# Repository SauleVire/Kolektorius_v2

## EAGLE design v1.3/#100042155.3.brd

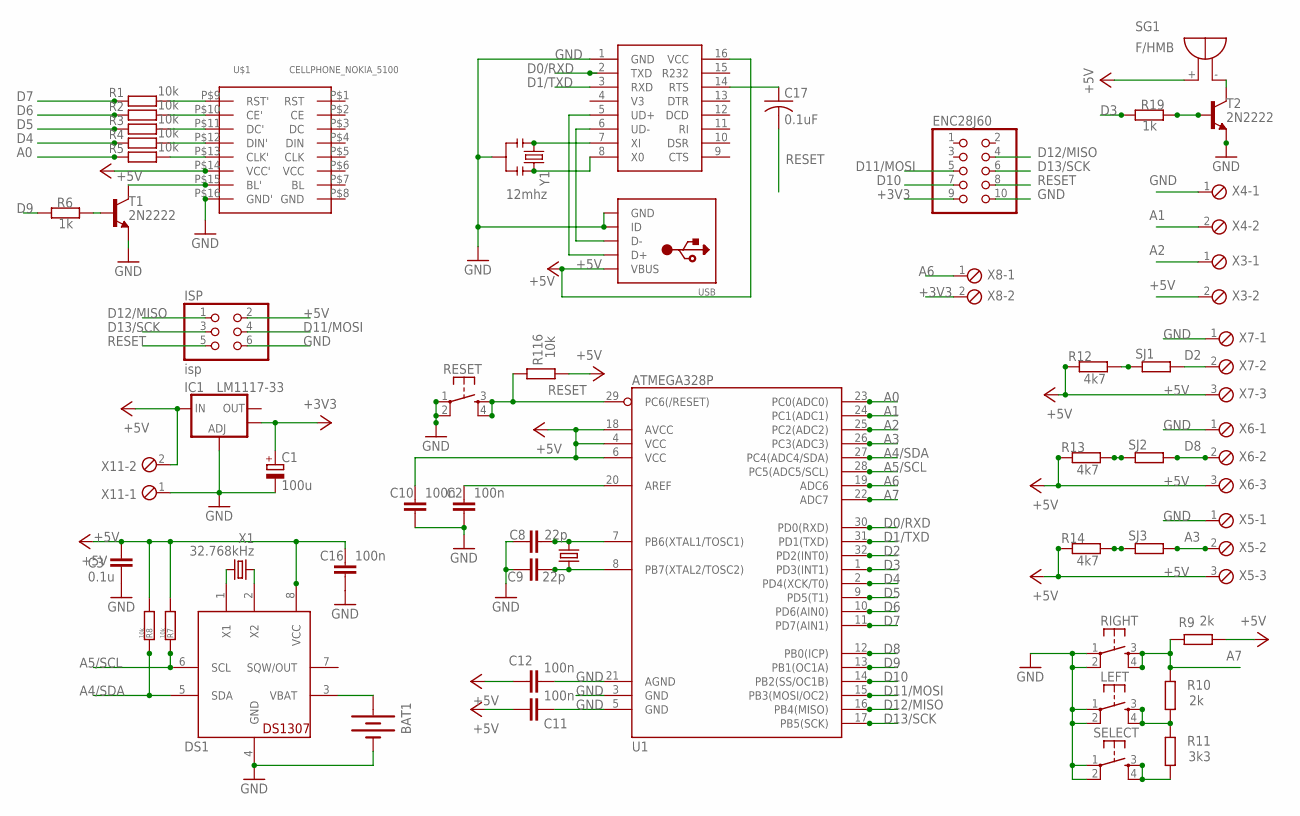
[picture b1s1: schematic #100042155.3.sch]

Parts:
BAT1: BATTCOM_20MM_PTH
C1: 100u; E2-5
C2, C10, C11, C12, C16: 100n; C0805
C3: 0.1u; C0805
C8, C9: 22p; C0805
C17: 0.1uF; C0805K
DS1: DS1307; SO08
ENC28J60: 2X05
IC1: LM1117-33; SOT223
ISP: isp; 2X03
LEFT: TACTILE-PTH
R1, R2, R3, R4, R5, R7, R8, R116: 10k; R0805
R6, R19: 1k; R0805
R9, R10: 2k; R0805
R11: 3k3; R0805
R12, R13, R14: 4k7; R0805
RESET: TAC_SWITCHPTH; TACTILE-PTH
RIGHT: TACTILE-PTH
SELECT: TACTILE-PTH
SG1: F/HMB
SJ1, SJ2, SJ3: R0402
T1, T2: 2N2222; TO92-EBC-OVAL
U1: ATMEGA328P; TQFP32-08
U$1: CELLPHONE_NOKIA_5100; CELLPHONE_NOKIA_5100_SPARKFUN
U$2: CH340G; SO016
USB: USB-MINIB-THM-MOLEX
X1: 32.768kHz; TC26H
X2: 16MHz; HC49US
X3, X4, X8, X11: 2POL254
X5, X6, X7: 3POL254
Y1: 12mhz; RESONATOR-PTH

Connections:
+3V3: C1.+, ENC28J60.9, IC1.4 (OUT), X8.2
+5V: C3.1, C10.1, C11.2, C12.2, C16.1, DS1.8 (VCC), IC1.3 (IN), ISP.2, R7.2, R8.2, R9.2, R12.1, R13.1, R14.1, R116.2, SG1.+, U1.4 (VCC), U1.6 (VCC), U1.18 (AVCC), U$1.P$14 (VCC'), U$2.16 (VCC), USB.VBUS, X3.2, X5.3, X6.3, X7.3, X11.2
A0: R5.1, U1.23 (PC0(ADC0))
A1: U1.24 (PC1(ADC1)), X4.2
A2: U1.25 (PC2(ADC2)), X3.1
A3: SJ3.2, U1.26 (PC3(ADC3)), X5.2
A4/SDA: DS1.5 (SDA), R8.1, U1.27 (PC4(ADC4/SDA))
A5/SCL: DS1.6 (SCL), R7.1, U1.28 (PC5(ADC5/SCL))
A6: U1.19 (ADC6), X8.1
A7: R9.1, R10.2, RIGHT.3, RIGHT.4, U1.22 (ADC7)
AREF: C2.1, U1.20 (AREF)
D0/RXD: U1.30 (PD0(RXD)), U$2.2 (TXD)
D1/TXD: U1.31 (PD1(TXD)), U$2.3 (RXD)
D2: SJ1.2, U1.32 (PD2(INT0)), X7.2
D3: R19.2, U1.1 (PD3(INT1))
D4: R4.1, U1.2 (PD4(XCK/T0))
D5: R3.1, U1.9 (PD5(T1))
D6: R2.1, U1.10 (PD6(AIN0))
D7: R1.1, U1.11 (PD7(AIN1))
D8: SJ2.2, U1.12 (PB0(ICP)), X6.2
D9: R6.2, U1.13 (PB1(OC1A))
D10: ENC28J60.7, U1.14 (PB2(SS/OC1B))
D11/MOSI: ENC28J60.5, ISP.4, U1.15 (PB3(MOSI/OC2))
D12/MISO: ENC28J60.4, ISP.1, U1.16 (PB4(MISO))
D13/SCK: ENC28J60.6, ISP.3, U1.17 (PB5(SCK))
GND: BAT1.2 (-), C1.-, C2.2, C3.2, C8.1, C9.1, C10.2, C11.1, C12.1, C16.2, DS1.4 (GND), ENC28J60.10, IC1.1 (ADJ), ISP.6, LEFT.1, LEFT.2, RESET.1, RESET.2, RIGHT.1, RIGHT.2, SELECT.1, SELECT.2, T1.E, T2.E, U1.3 (GND), U1.5 (GND), U1.21 (AGND), U$1.P$16 (GND'), U$2.1 (GND), USB.GND, USB.ID, X4.1, X5.1, X6.1, X7.1, X11.1, Y1.2
unnamed: LEFT.3, LEFT.4, R10.1, R11.2
unnamed: R5.2, U$1.P$13 (CLK')
unnamed: R4.2, U$1.P$12 (DIN')
unnamed: R3.2, U$1.P$11 (DC')
unnamed: R2.2, U$1.P$10 (CE')
unnamed: R1.2, U$1.P$9 (RST')
unnamed: BAT1.1 (+), DS1.3 (VBAT)
unnamed: DS1.1 (X1), X1.2
unnamed: U$2.7 (XI), Y1.1
unnamed: U$2.6 (UD-), USB.D-
unnamed: U$2.5 (UD+), USB.D+
unnamed: R13.2, SJ2.1
unnamed: R11.1, SELECT.3, SELECT.4
unnamed: T1.C, U$1.P$15 (BL')
unnamed: R19.1, T2.B
unnamed: R14.2, SJ3.1
unnamed: SG1.-, T2.C
unnamed: DS1.2 (X2), X1.1
unnamed: R12.2, SJ1.1
unnamed: C9.2, U1.8 (PB7(XTAL2/TOSC2)), X2.1
unnamed: C8.2, U1.7 (PB6(XTAL1/TOSC1)), X2.2
unnamed: U$2.8 (X0), Y1.3
unnamed: C17.1, U$2.14 (RTS)
unnamed: R6.1, T1.B
RESET: C17.2, ENC28J60.8, ISP.5, R116.1, RESET.3, RESET.4, U1.29 (PC6(/RESET))

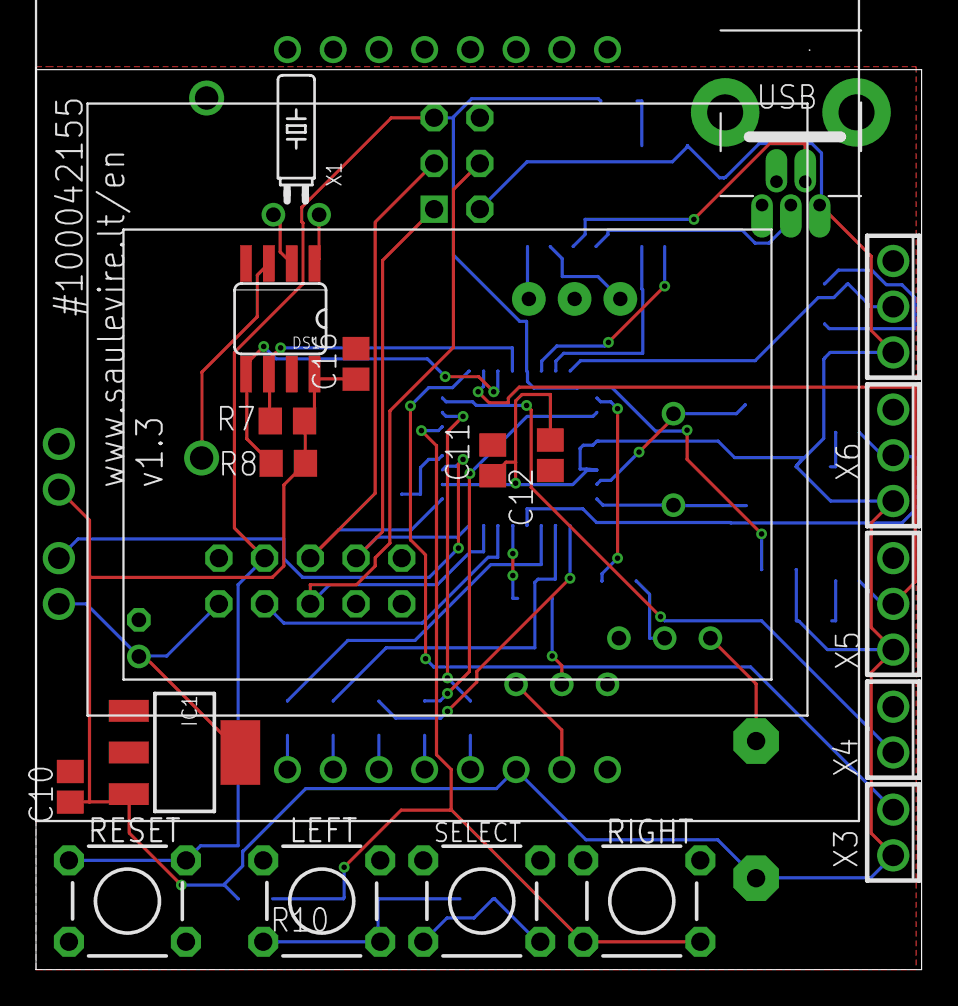
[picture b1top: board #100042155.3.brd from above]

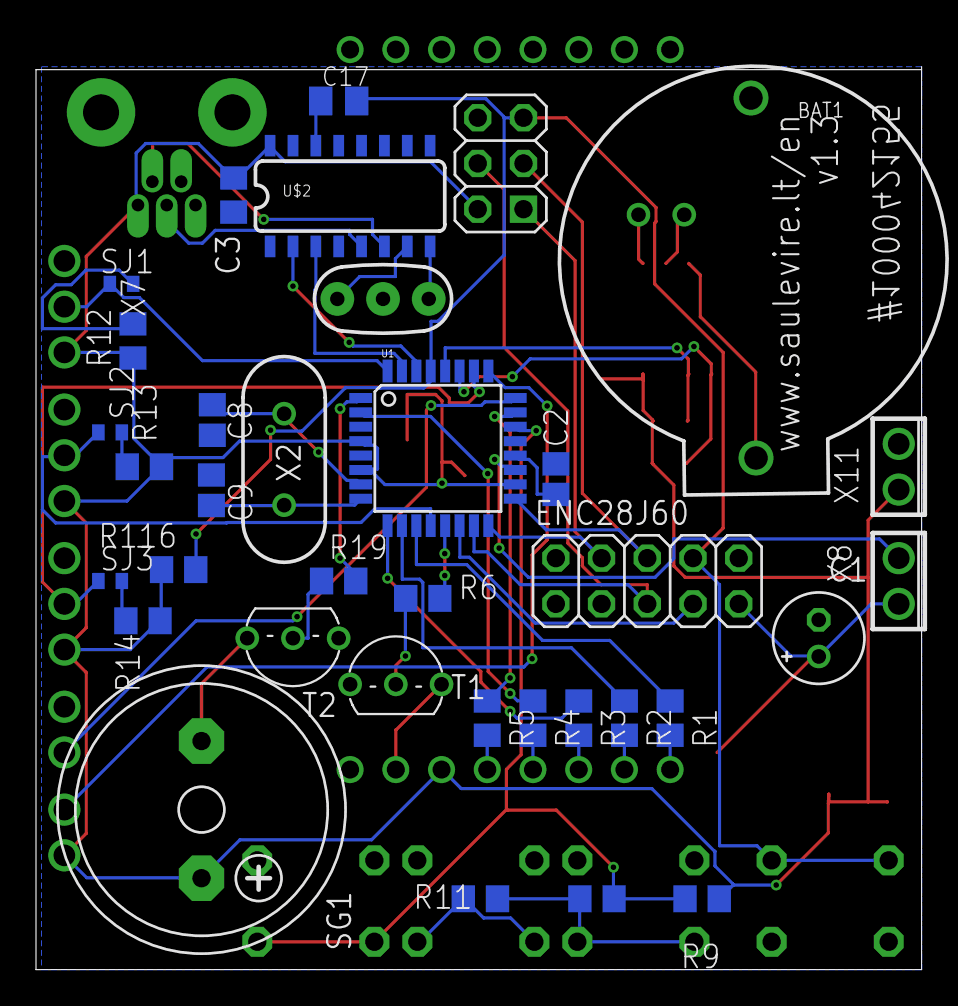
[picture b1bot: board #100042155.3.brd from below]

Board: 2 copper layers, 49.2 x 50.2 mm, 55 parts (35 on the bottom side), 51 nets.

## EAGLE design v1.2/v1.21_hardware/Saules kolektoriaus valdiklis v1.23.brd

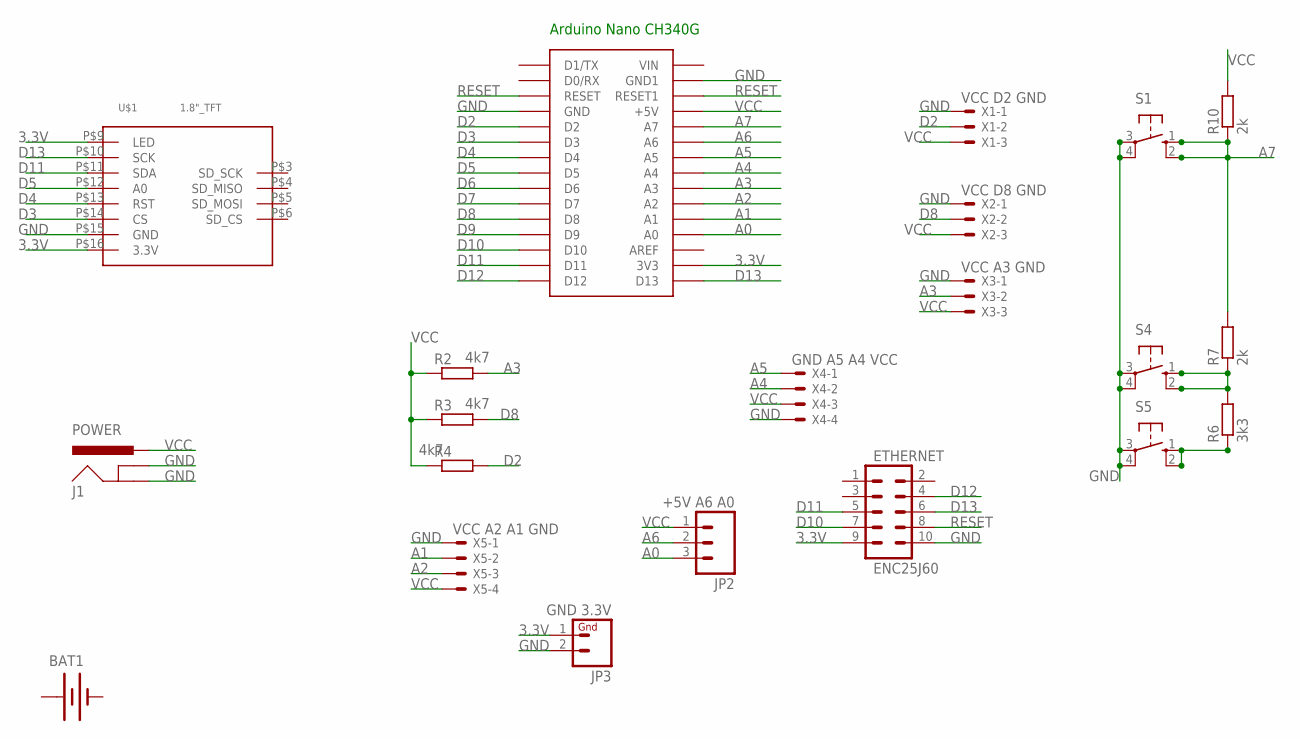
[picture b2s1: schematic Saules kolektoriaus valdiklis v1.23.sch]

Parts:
ARDUINONANOCH340G: ARDUINONANO; PDIP-32
BAT1: BATTERY20PTH; BATTCOM_20MM_PTH
ETHERNET: ENC25J60; AVR_ICSP
J1: POWER; POWER_JACK_PTH_LOCK
JP2: +5V A6 A0; 1X03
JP3: GND 3.3V; 1X02
R2, R3, R4: 4k7; 0207/10
R6: 3k3; 0207/10
R7, R10: 2k; 0207/10
S1, S4, S5: 10-XX; B3F-10XX
U$1: 1.8"_TFT
X1: VCC D2 GND; 22-23-2031
X2: VCC D8 GND; 22-23-2031
X3: VCC A3 GND; 22-23-2031
X4: GND A5 A4 VCC; 22-23-2041
X5: VCC A2 A1 GND; 22-23-2041

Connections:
3.3V: ARDUINONANOCH340G.3V3, ETHERNET.9, JP3.1, U$1.P$9 (LED), U$1.P$16 (3.3V)
+: BAT1.1 (+)
-: BAT1.2 (-)
A0: ARDUINONANOCH340G.A0, JP2.3
A1: ARDUINONANOCH340G.A1, X5.2
A2: ARDUINONANOCH340G.A2, X5.3
A3: ARDUINONANOCH340G.A3, R2.2, X3.2
A4: ARDUINONANOCH340G.A4, X4.2
A5: ARDUINONANOCH340G.A5, X4.1
A6: ARDUINONANOCH340G.A6, JP2.2
A7: ARDUINONANOCH340G.A7, R7.2, R10.1, S1.1 (S), S1.2 (S1)
D2: ARDUINONANOCH340G.D2, R4.2, X1.2
D3: ARDUINONANOCH340G.D3, U$1.P$14 (CS)
D4: ARDUINONANOCH340G.D4, U$1.P$13 (RST)
D5: ARDUINONANOCH340G.D5, U$1.P$12 (A0)
D6: ARDUINONANOCH340G.D6
D7: ARDUINONANOCH340G.D7
D8: ARDUINONANOCH340G.D8, R3.2, X2.2
D9: ARDUINONANOCH340G.D9
D10: ARDUINONANOCH340G.D10, ETHERNET.7
D11: ARDUINONANOCH340G.D11, ETHERNET.5, U$1.P$11 (SDA)
D12: ARDUINONANOCH340G.D12, ETHERNET.4
D13: ARDUINONANOCH340G.D13, ETHERNET.6, U$1.P$10 (SCK)
GND: ARDUINONANOCH340G.GND, ARDUINONANOCH340G.GND1, ETHERNET.10, J1.GND, J1.GNDBREAK, JP3.2, S1.3, S1.4 (P1), S4.3, S4.4 (P1), S5.3, S5.4 (P1), U$1.P$15 (GND), X1.1, X2.1, X3.1, X4.4, X5.1
unnamed: R6.1, S5.1 (S), S5.2 (S1)
unnamed: R6.2, R7.1, S4.1 (S), S4.2 (S1)
RESET: ARDUINONANOCH340G.RESET, ARDUINONANOCH340G.RESET1, ETHERNET.8
VCC: ARDUINONANOCH340G.+5V, J1.PWR, JP2.1, R2.1, R3.1, R4.1, R10.2, X1.3, X2.3, X3.3, X4.3, X5.4

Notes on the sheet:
Arduino Nano CH340G

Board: 2 copper layers, 21 parts (2 on the bottom side), 23 nets, no tracks yet.

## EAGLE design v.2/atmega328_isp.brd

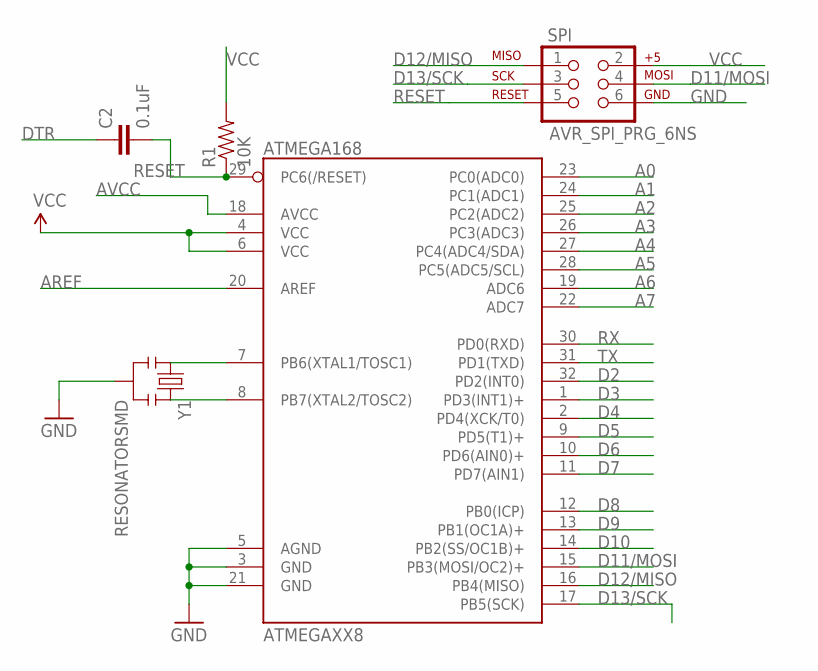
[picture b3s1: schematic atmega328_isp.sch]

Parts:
ATMEGAXX8: ATMEGA168; TQFP32-08
C2: 0.1uF; 0805
R1: 10K; 0805
SPI: AVR_SPI_PRG_6NS; 2X3-NS
Y1: RESONATORSMD; RESONATOR-SMD

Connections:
A0: ATMEGAXX8.23 (PC0(ADC0))
A1: ATMEGAXX8.24 (PC1(ADC1))
A2: ATMEGAXX8.25 (PC2(ADC2))
A3: ATMEGAXX8.26 (PC3(ADC3))
A4: ATMEGAXX8.27 (PC4(ADC4/SDA))
A5: ATMEGAXX8.28 (PC5(ADC5/SCL))
A6: ATMEGAXX8.19 (ADC6)
A7: ATMEGAXX8.22 (ADC7)
AREF: ATMEGAXX8.20 (AREF)
AVCC: ATMEGAXX8.18 (AVCC)
D2: ATMEGAXX8.32 (PD2(INT0))
D3: ATMEGAXX8.1 (PD3(INT1)+)
D4: ATMEGAXX8.2 (PD4(XCK/T0))
D5: ATMEGAXX8.9 (PD5(T1)+)
D6: ATMEGAXX8.10 (PD6(AIN0)+)
D7: ATMEGAXX8.11 (PD7(AIN1))
D8: ATMEGAXX8.12 (PB0(ICP))
D9: ATMEGAXX8.13 (PB1(OC1A)+)
D10: ATMEGAXX8.14 (PB2(SS/OC1B)+)
D11/MOSI: ATMEGAXX8.15 (PB3(MOSI/OC2)+), SPI.4
D12/MISO: ATMEGAXX8.16 (PB4(MISO)), SPI.1
D13/SCK: ATMEGAXX8.17 (PB5(SCK)), SPI.3
DTR: C2.1
GND: ATMEGAXX8.3 (GND), ATMEGAXX8.5 (AGND), ATMEGAXX8.21 (GND), SPI.6, Y1.2
RESET: ATMEGAXX8.29 (PC6(/RESET)), C2.2, R1.1, SPI.5
RX: ATMEGAXX8.30 (PD0(RXD))
TX: ATMEGAXX8.31 (PD1(TXD))
VCC: ATMEGAXX8.4 (VCC), ATMEGAXX8.6 (VCC), R1.2, SPI.2
XTAL1: ATMEGAXX8.7 (PB6(XTAL1/TOSC1)), Y1.1
XTAL2: ATMEGAXX8.8 (PB7(XTAL2/TOSC2)), Y1.3

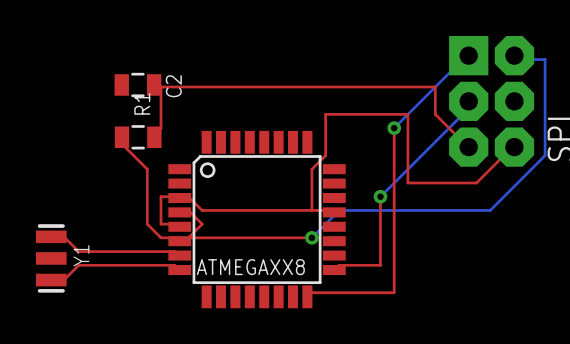
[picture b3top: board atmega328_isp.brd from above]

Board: 2 copper layers, 5 parts (0 on the bottom side), 8 nets.

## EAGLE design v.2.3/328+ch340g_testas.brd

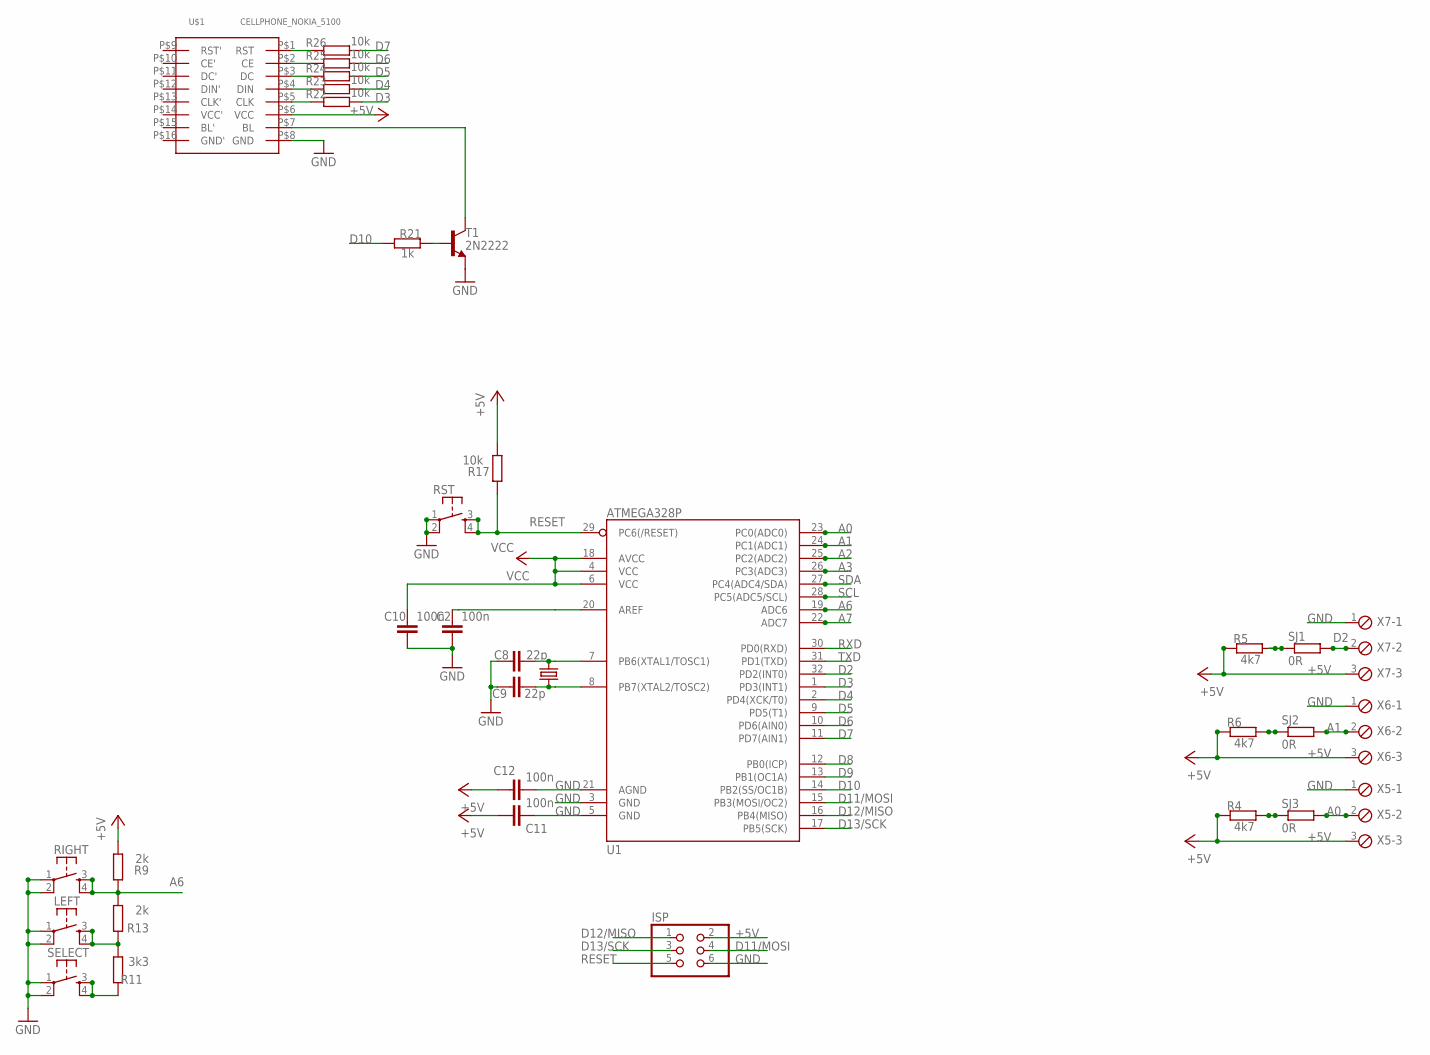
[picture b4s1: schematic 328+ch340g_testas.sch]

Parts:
C2, C10, C11, C12: 100n; C0805
C8, C9: 22p; C0805
ISP: PINHD-2X3; 2X03
LEFT: TAC_SWITCHPTH; TACTILE-PTH
R4, R5, R6: 4k7; R0805
R9, R13: 2k; R0805
R11: 3k3; R0805
R17, R22, R23, R24, R25, R26: 10k; R0805
R21: 1k; R0805
RIGHT: TAC_SWITCHPTH; TACTILE-PTH
RST: TAC_SWITCHPTH; TACTILE-PTH
SELECT: TAC_SWITCHPTH; TACTILE-PTH
SJ1, SJ2, SJ3: 0R; R0402
T1: 2N2222; TO92-EBC-OVAL
U1: ATMEGA328P; TQFP32-08
U$1: CELLPHONE_NOKIA_5100; CELLPHONE_NOKIA_5100_SPARKFUN
X2: 16MHz; HC49US
X5, X6, X7: MPT3; 3POL254

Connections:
+5V: C11.2, C12.2, ISP.2, R4.1, R5.1, R6.1, R9.2, R17.2, U$1.P$6 (VCC), X5.3, X6.3, X7.3
A0: SJ3.2, U1.23 (PC0(ADC0)), X5.2
A1: SJ2.2, U1.24 (PC1(ADC1)), X6.2
A2: U1.25 (PC2(ADC2))
A3: U1.26 (PC3(ADC3))
A6: R9.1, R13.2, RIGHT.3, RIGHT.4, U1.19 (ADC6)
A7: U1.22 (ADC7)
D2: SJ1.2, U1.32 (PD2(INT0)), X7.2
D3: R22.2, U1.1 (PD3(INT1))
D4: R23.2, U1.2 (PD4(XCK/T0))
D5: R24.2, U1.9 (PD5(T1))
D6: R25.2, U1.10 (PD6(AIN0))
D7: R26.2, U1.11 (PD7(AIN1))
D8: U1.12 (PB0(ICP))
D9: U1.13 (PB1(OC1A))
D10: R21.2, U1.14 (PB2(SS/OC1B))
D11/MOSI: ISP.4, U1.15 (PB3(MOSI/OC2))
D12/MISO: ISP.1, U1.16 (PB4(MISO))
D13/SCK: ISP.3, U1.17 (PB5(SCK))
GND: C2.2, C8.1, C9.1, C10.2, C11.1, C12.1, ISP.6, LEFT.1, LEFT.2, RIGHT.1, RIGHT.2, RST.1, RST.2, SELECT.1, SELECT.2, T1.E, U1.3 (GND), U1.5 (GND), U1.21 (AGND), U$1.P$8 (GND), X5.1, X6.1, X7.1
unnamed: LEFT.3, LEFT.4, R11.2, R13.1
unnamed: R6.2, SJ2.1
unnamed: R11.1, SELECT.3, SELECT.4
unnamed: R22.1, U$1.P$5 (CLK)
unnamed: R25.1, U$1.P$2 (CE)
unnamed: R24.1, U$1.P$3 (DC)
unnamed: R23.1, U$1.P$4 (DIN)
unnamed: T1.C, U$1.P$7 (BL)
unnamed: R4.2, SJ3.1
unnamed: R5.2, SJ1.1
unnamed: C9.2, U1.8 (PB7(XTAL2/TOSC2)), X2.1
unnamed: C8.2, U1.7 (PB6(XTAL1/TOSC1)), X2.2
unnamed: C2.1, U1.20 (AREF)
unnamed: R21.1, T1.B
RESET: ISP.5, R17.1, RST.3, RST.4, U1.29 (PC6(/RESET))
RXD: U1.30 (PD0(RXD))
SCL: U1.28 (PC5(ADC5/SCL))
SDA: U1.27 (PC4(ADC4/SDA))
TXD: U1.31 (PD1(TXD))
V$: R26.1, U$1.P$1 (RST)
VCC: C10.1, U1.4 (VCC), U1.6 (VCC), U1.18 (AVCC)

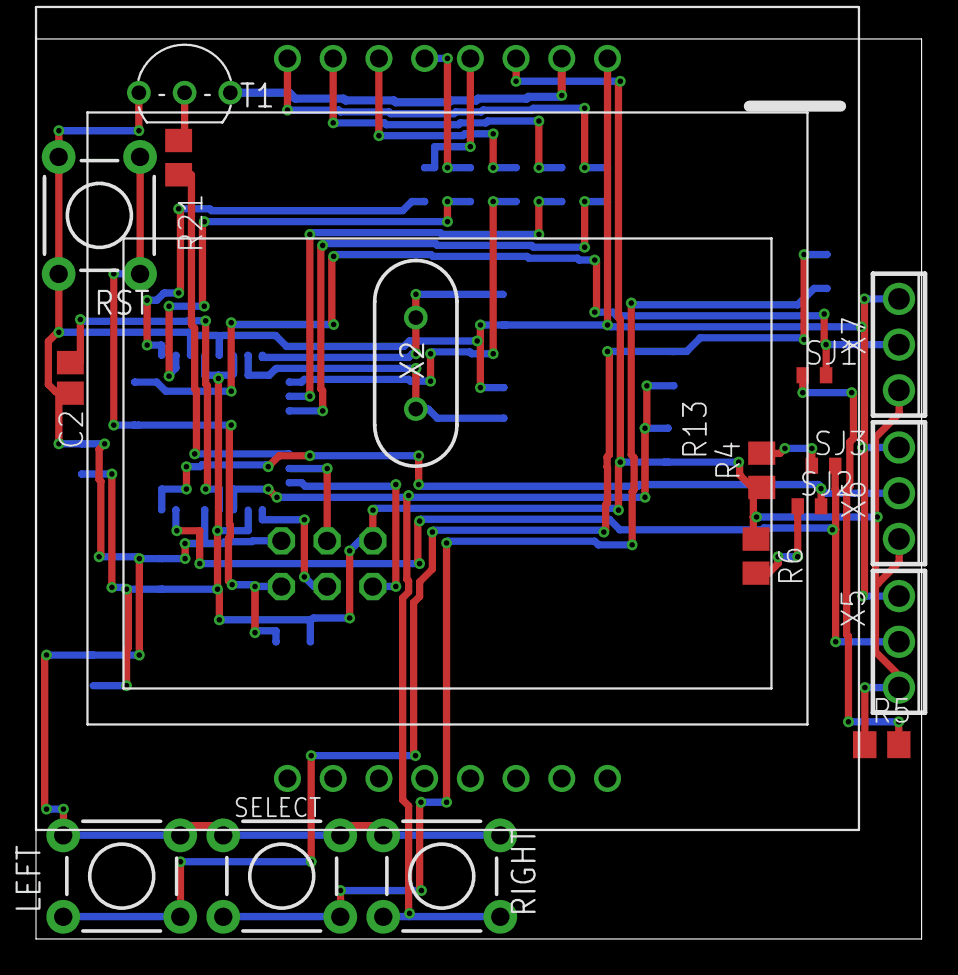
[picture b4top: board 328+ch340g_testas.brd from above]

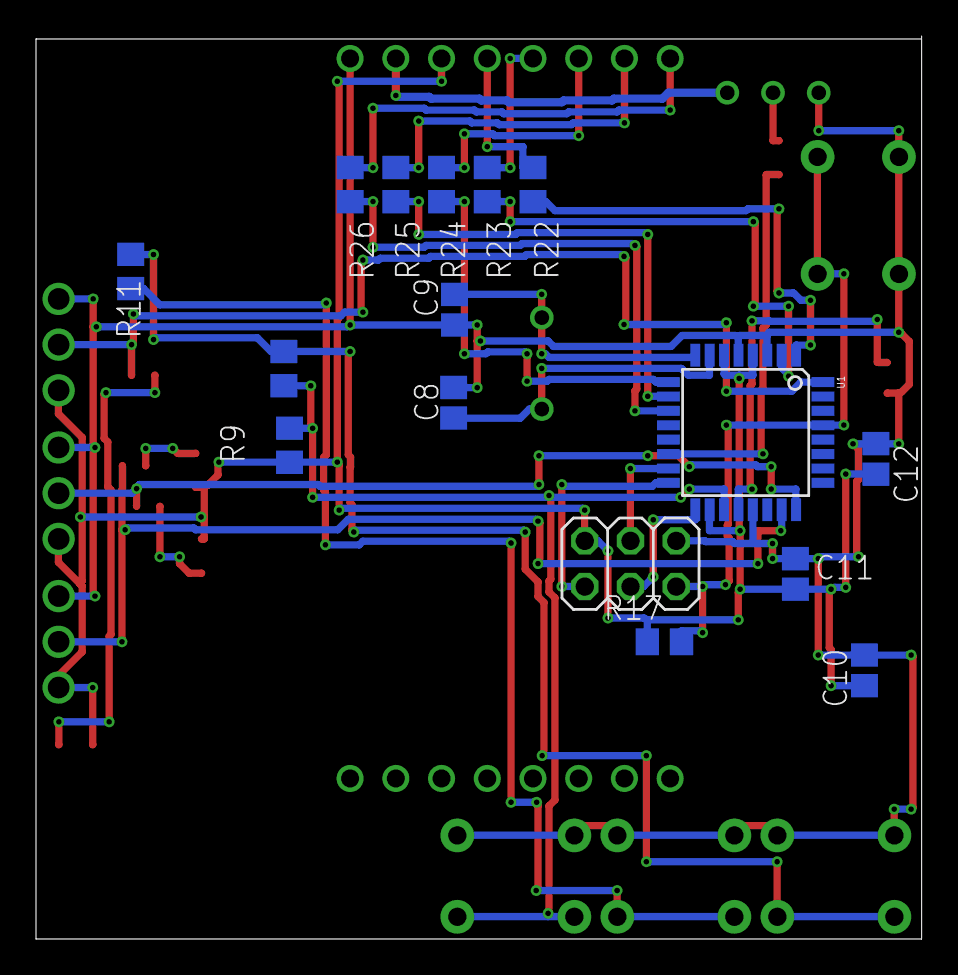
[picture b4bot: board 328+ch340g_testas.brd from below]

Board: 2 copper layers, 49.2 x 50.2 mm, 34 parts (16 on the bottom side), 32 nets.

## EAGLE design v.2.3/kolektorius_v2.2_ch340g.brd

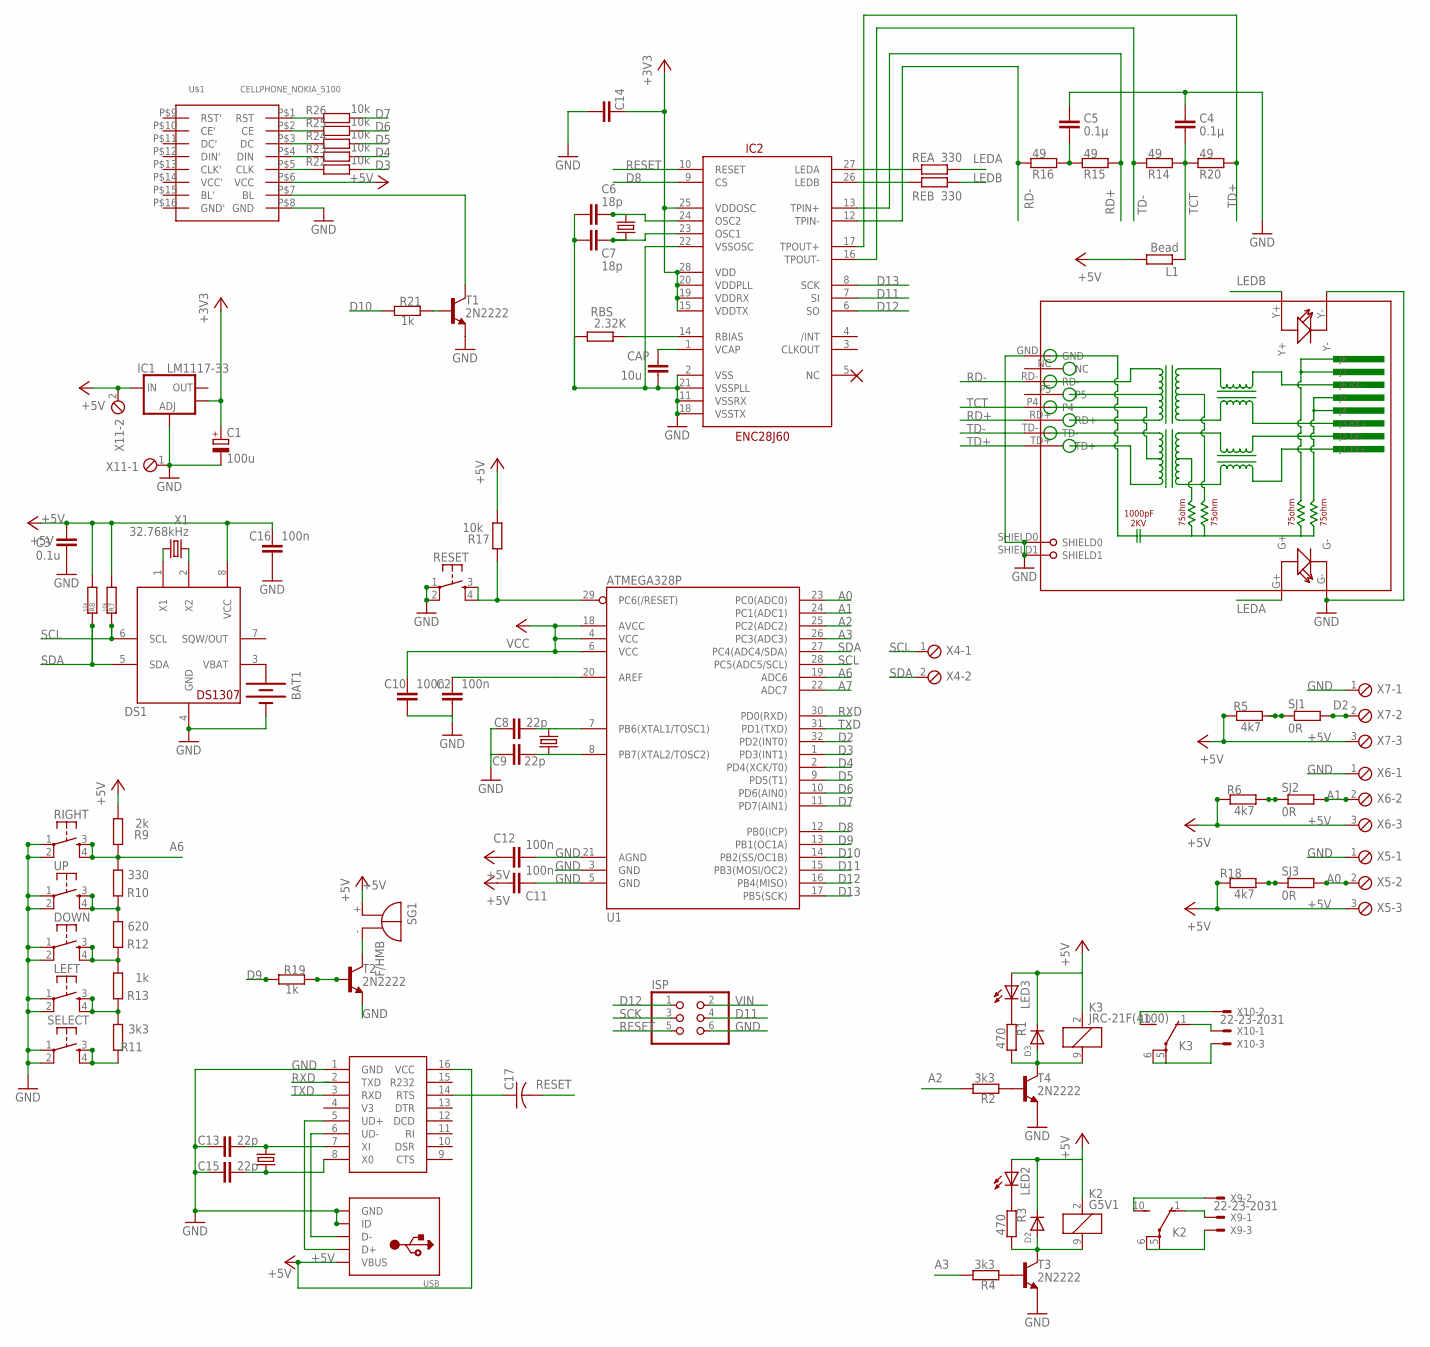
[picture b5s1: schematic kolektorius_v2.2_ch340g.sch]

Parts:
BAT1: BATTERY20PTH; BATTCOM_20MM_PTH
C1: 100u; E2-5
C2, C10, C11, C12, C14, C16: 100n; C0805
C3: 0.1u; C0805
C4, C5: 0.1µ; C0805
C6, C7: 18p; C0805
C8, C9, C13, C15: 22p; C0805
C17: C-USC0805K; C0805K
CAP: 10u; C0805
D2, D3: DIODEDO-1N4148; DO-1N4148
DOWN: TAC_SWITCHPTH; TACTILE-PTH
DS1: DS1307; SO08
IC1: LM1117-33; SOT223
IC2: ENC28J60; SSOP28DB
ISP: PINHD-2X3; 2X03
K2: G5V1
K3: JRC-21F(4100); G5V1
L1: Bead; R0805
LED2, LED3: LEDSMT1206; 1206
LEFT: TAC_SWITCHPTH; TACTILE-PTH
R1, R3: 470; R0805
R2, R4, R11: 3k3; R0805
R5, R6, R18: 4k7; R0805
R7, R8, R17, R22, R23, R24, R25, R26: 10k; R0805
R9: 2k; R0805
R10: 330; R0805
R12: 620; R0805
R13, R19, R21: 1k; R0805
R14, R15, R16, R20: 49; R0805
RBS: 2.32K; R0805
REA: 330; R0805
REB: 330; R0805
RESET: TAC_SWITCHPTH; TACTILE-PTH
RIGHT: TAC_SWITCHPTH; TACTILE-PTH
RJ1: HR911105A
SELECT: TAC_SWITCHPTH; TACTILE-PTH
SG1: F/HMB
SJ1, SJ2, SJ3: 0R; R0402
T1, T2, T3, T4: 2N2222; TO92-EBC-OVAL
U1: ATMEGA328P; TQFP32-08
U$1: CELLPHONE_NOKIA_5100; CELLPHONE_NOKIA_5100_SPARKFUN
U$2: CH340G; SO016
UP: TAC_SWITCHPTH; TACTILE-PTH
USB: USBMOLEX; USB-MINIB-THM-MOLEX
X1: 32.768kHz; TC26H
X2, X12: 16MHz; HC49US
X3: 25MHz; HC49US
X4, X11: MPT2; 2POL254
X5, X6, X7: MPT3; 3POL254
X9, X10: 22-23-2031

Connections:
+3V3: C1.+, C14.1, IC1.4 (OUT), IC2.15 (VDDTX), IC2.19 (VDDRX), IC2.20 (VDDPLL), IC2.25 (VDDOSC), IC2.28 (VDD)
+5V: C3.1, C10.1, C11.2, C12.2, C16.1, D2.C, D3.C, DS1.8 (VCC), IC1.3 (IN), K2.2 (1), K3.2 (1), L1.2, LED2.A, LED3.A, R5.1, R6.1, R7.2, R8.2, R9.2, R17.2, R18.1, SG1.+, U1.4 (VCC), U1.6 (VCC), U1.18 (AVCC), U$1.P$6 (VCC), U$2.16 (VCC), USB.VBUS, X5.3, X6.3, X7.3, X11.2
A0: SJ3.2, U1.23 (PC0(ADC0)), X5.2
A1: SJ2.2, U1.24 (PC1(ADC1)), X6.2
A2: R2.2, U1.25 (PC2(ADC2))
A3: R4.2, U1.26 (PC3(ADC3))
A6: R9.1, R10.2, RIGHT.3, RIGHT.4, U1.19 (ADC6)
A7: U1.22 (ADC7)
D2: SJ1.2, U1.32 (PD2(INT0)), X7.2
D3: R22.2, U1.1 (PD3(INT1))
D4: R23.2, U1.2 (PD4(XCK/T0))
D5: R24.2, U1.9 (PD5(T1))
D6: R25.2, U1.10 (PD6(AIN0))
D7: R26.2, U1.11 (PD7(AIN1))
D8: IC2.9 (CS), U1.12 (PB0(ICP))
D9: R19.2, U1.13 (PB1(OC1A))
D10: R21.2, U1.14 (PB2(SS/OC1B))
D11: IC2.7 (SI), ISP.4, U1.15 (PB3(MOSI/OC2))
D12: IC2.6 (SO), ISP.1, U1.16 (PB4(MISO))
D13: IC2.8 (SCK), U1.17 (PB5(SCK))
GND: BAT1.2 (-), C1.-, C2.2, C3.2, C4.1, C5.1, C6.2, C7.2, C8.1, C9.1, C10.2, C11.1, C12.1, C13.1, C14.2, C15.1, C16.2, CAP.2, DOWN.1, DOWN.2, DS1.4 (GND), IC1.1 (ADJ), IC2.2 (VSS), IC2.11 (VSSRX), IC2.18 (VSSTX), IC2.21 (VSSPLL), IC2.22 (VSSOSC), ISP.6, LEFT.1, LEFT.2, RBS.1, RESET.1, RESET.2, RIGHT.1, RIGHT.2, RJ1.G-, RJ1.GND, RJ1.SHIELD0, RJ1.SHIELD1, RJ1.Y-, SELECT.1, SELECT.2, T1.E, T2.E, T3.E, T4.E, U1.3 (GND), U1.5 (GND), U1.21 (AGND), U$1.P$8 (GND), U$2.1 (GND), UP.1, UP.2, USB.GND, USB.ID, X5.1, X6.1, X7.1, X11.1
LEDA: REA.2, RJ1.G+
LEDB: REB.2, RJ1.Y+
unnamed: LEFT.3, LEFT.4, R11.2, R13.1
unnamed: D2.A, K2.9 (2), R3.2, T3.C
unnamed: R4.1, T3.B
unnamed: K2.5, K2.6, X9.3
unnamed: K2.10 (S), X9.2
unnamed: DOWN.3, DOWN.4, R12.1, R13.2
unnamed: LED2.C, R3.1
unnamed: DS1.1 (X1), X1.2
unnamed: R10.1, R12.2, UP.3, UP.4
unnamed: C13.2, U$2.7 (XI), X12.2
unnamed: U$2.6 (UD-), USB.D-
unnamed: D3.A, K3.9 (2), R1.2, T4.C
unnamed: R2.1, T4.B
unnamed: K2.1 (O), X9.1
unnamed: U$2.5 (UD+), USB.D+
unnamed: K3.10 (S), X10.2
unnamed: R6.2, SJ2.1
unnamed: R11.1, SELECT.3, SELECT.4
unnamed: K3.5, K3.6, X10.3
unnamed: K3.1 (O), X10.1
unnamed: LED3.C, R1.1
unnamed: R22.1, U$1.P$5 (CLK)
unnamed: R25.1, U$1.P$2 (CE)
unnamed: R24.1, U$1.P$3 (DC)
unnamed: R23.1, U$1.P$4 (DIN)
unnamed: T1.C, U$1.P$7 (BL)
unnamed: R19.1, T2.B
unnamed: R18.2, SJ3.1
unnamed: SG1.-, T2.C
unnamed: DS1.2 (X2), X1.1
unnamed: R5.2, SJ1.1
unnamed: C9.2, U1.8 (PB7(XTAL2/TOSC2)), X2.1
unnamed: C8.2, U1.7 (PB6(XTAL1/TOSC1)), X2.2
unnamed: IC2.27 (LEDA), REA.1
unnamed: C2.1, U1.20 (AREF)
unnamed: BAT1.1 (+), DS1.3 (VBAT)
unnamed: IC2.26 (LEDB), REB.1
unnamed: CAP.1, IC2.1 (VCAP)
unnamed: C15.2, U$2.8 (X0), X12.1
unnamed: C6.1, IC2.24 (OSC2), X3.2
unnamed: C7.1, IC2.23 (OSC1), X3.1
unnamed: C17.1, U$2.14 (RTS)
unnamed: R21.1, T1.B
unnamed: R17.1, RESET.3, RESET.4, U1.29 (PC6(/RESET))
unnamed: C5.2, R15.1, R16.2
unnamed: IC2.14 (RBIAS), RBS.2
RD+: IC2.13 (TPIN+), R15.2, RJ1.RD+
RD-: IC2.12 (TPIN-), R16.1, RJ1.RD-
RESET: C17.2, IC2.10 (RESET), ISP.5
RXD: U1.30 (PD0(RXD))
SCK: ISP.3
SCL: DS1.6 (SCL), R7.1, U1.28 (PC5(ADC5/SCL)), X4.1
SDA: DS1.5 (SDA), R8.1, U1.27 (PC4(ADC4/SDA)), X4.2
TCT: C4.2, L1.1, R14.2, R20.1, RJ1.P4
TD+: IC2.17 (TPOUT+), R20.2, RJ1.TD+
TD-: IC2.16 (TPOUT-), R14.1, RJ1.TD-
TXD: U1.31 (PD1(TXD)), U$2.3 (RXD)
V$: R26.1, U$1.P$1 (RST)
VIN: ISP.2

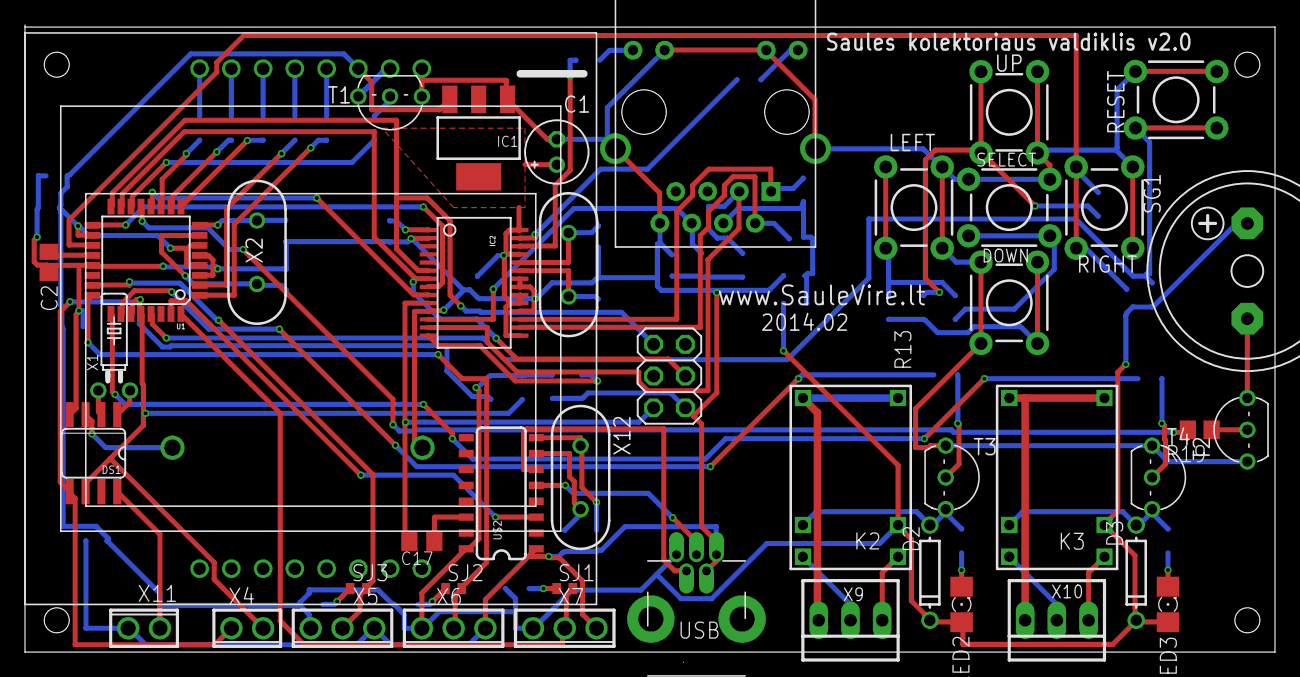
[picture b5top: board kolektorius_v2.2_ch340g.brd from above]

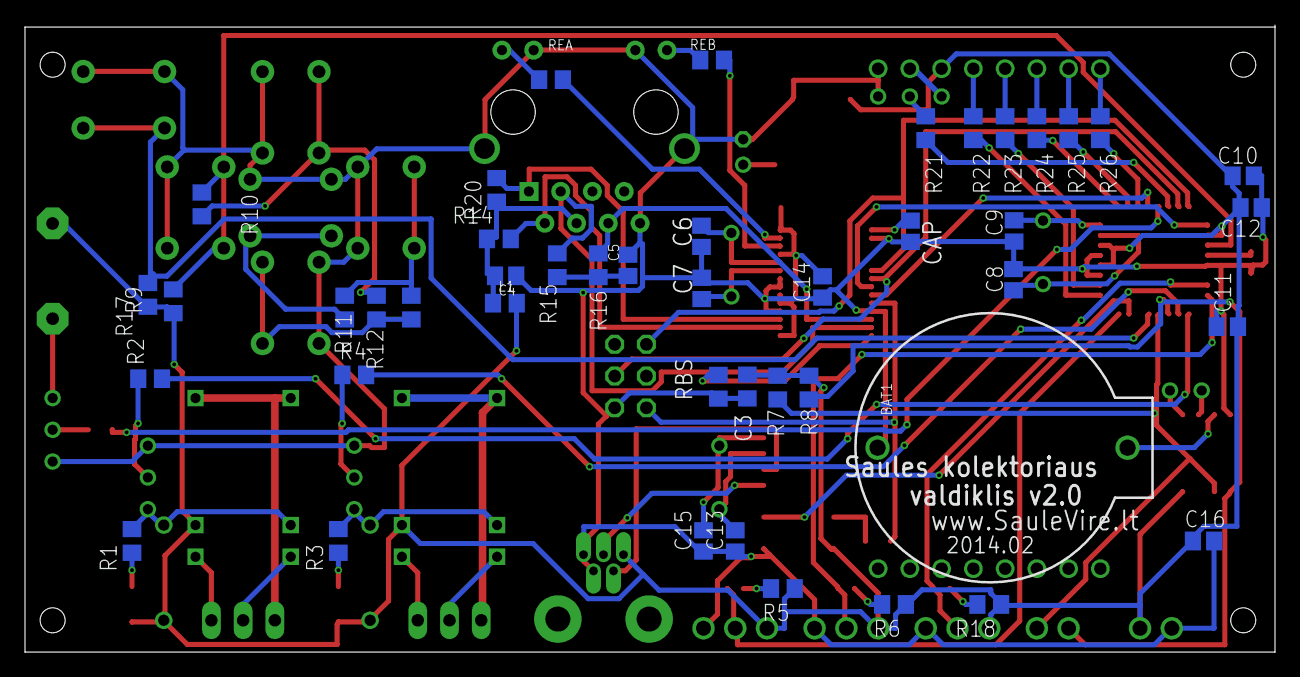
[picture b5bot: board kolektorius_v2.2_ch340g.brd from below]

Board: 2 copper layers, 100.0 x 50.2 mm, 89 parts (45 on the bottom side), 78 nets.

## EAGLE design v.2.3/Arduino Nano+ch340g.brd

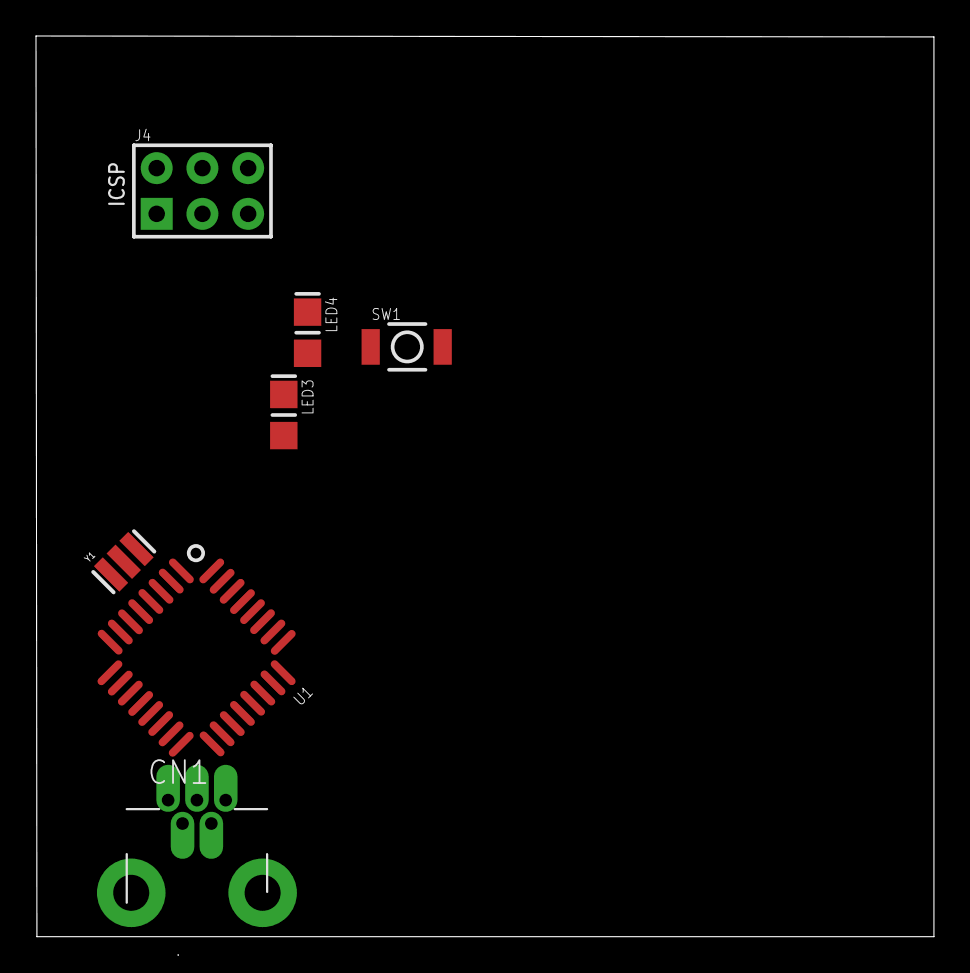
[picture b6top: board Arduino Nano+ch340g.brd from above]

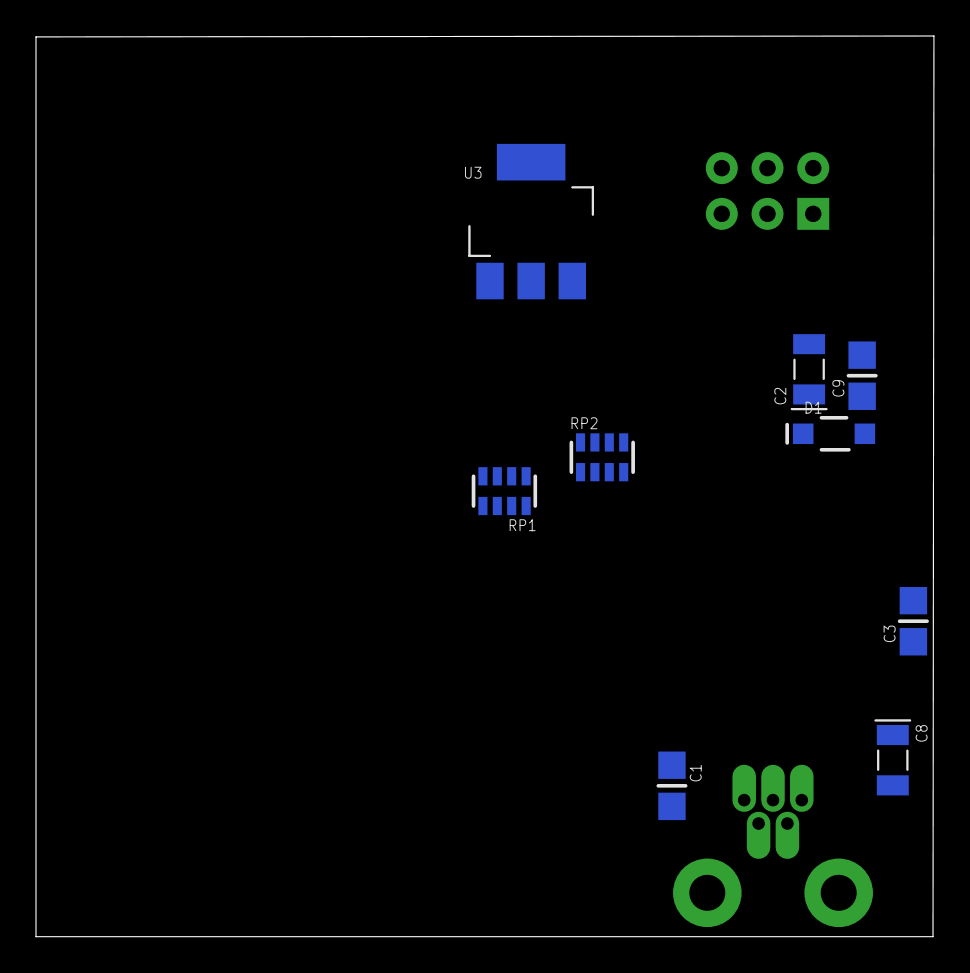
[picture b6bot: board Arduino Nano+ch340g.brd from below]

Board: 2 copper layers, 49.9 x 50.0 mm, 16 parts (9 on the bottom side), 14 nets, no tracks yet.

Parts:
C1, C3, C9: 0.1uF; CAP0805-NP
C2, C8: 4.7uF; TAN-A
CN1: USB-MINIB-THM-MOLEX
D1: MBR0520; SOD-123
J4: HEAD3X2
LED3: L_AMBER; LED0805
LED4: BLUE; LED0805
RP1: 1K; RES4NT
RP2: 330; RES4NT
SW1: RESET; 157SW
U1: ATMEGA168-20AU; QFP032
U3: UA78M05; SOT223
Y1: 16MHz; RESONATOR

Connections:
+5V: C2.1, C3.1, D1.1, J4.2, RP1.5, RP2.2, U1.4, U1.6, U1.18, U3.3
AREF: C1.1, U1.20
COM: C1.2, C2.2, C3.2, C8.2, C9.2, J4.6, LED3.1, LED4.1, SW1.1, U1.3, U1.5, U1.21, U3.2, U3.4, Y1.2
D0/RX: RP1.2, U1.30
D1/TX: RP1.3, U1.31
D11/MOSI: J4.4, U1.15
D12/MISO: J4.1, U1.16
D13/SCK: J4.3, RP2.1, U1.17
unnamed: U1.8, Y1.3
unnamed: U1.7, Y1.1
unnamed: LED4.2, RP2.7
unnamed: LED3.2, RP2.8
RESET: J4.5, RP1.4, SW1.2, U1.29
VUSB: C8.1, C9.1, D1.2

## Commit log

2014-01-07 pcb versija
2014-01-07 pridetas tinklas, 3.3v
2014-01-07 i6mestas pertraukimas
2014-01-08 pabaigta
2014-01-09 pastumdyta detalės...
2014-01-09 padaryta
2014-01-09 Finito, paruo6ta siuntimui
2014-02-04 v2-tikras
2014-02-04 pervarkymas katalogu
2014-02-04 pertvarkymas katalogu
2014-02-06 judam pirmyn
2014-02-11 pcb...
2014-02-11 pcb..
2014-02-13 pcb is naujo
2014-02-16 pcb
    prie pabaigos...
2014-02-18 pcb prie pabaigos
2014-03-02 v1.2 softas
2014-03-02 klaviatura
2014-03-03 n versija
2014-03-04 pirmyn....
2014-03-05 sutvarkyta
2014-03-05 einu pirmyn
2014-03-05 viskas veikia
2014-03-06 +lan
2014-03-06 + lan
2014-03-12 mazinu koda...
2014-03-13 ds18b20 be bibliotekos
2014-03-26 pataisyta brd
2014-03-26 pataisyta
2014-03-31 pabaiga
2014-06-24 prijungta prie tinklo emoncms
    veikiantis pvz
2014-10-30 versija v1.21
2014-10-31 gerber failai i6siuntimui
2014-11-01 padaryta nauja pcb su laikrodžiu ds1307
    išmetus 5V jungtį atsirado vietos ds1307 mikroschemai, maitinimas
    planuojamas per usb kabelį
2014-11-03 ch340G
2014-11-04 Paliktos 2 reles
2014-11-04 ištrintos tarpinės versijos
2014-11-04 pridėtas failas .gitignore
2014-11-04 pataisymai, paliktos 2 reles
2014-11-04 pataisymai
2014-11-04 pataisymai
    2 reles jrc-21f(4100)
2014-11-05 pataisymai, trasavimas
2014-11-10 pridėtas švilpukas
    išnaudoti visi kontaktai
2014-11-12 sutrasuota
2014-12-24 1.3 versija
    programa su 3 klavisais
2015-01-06 pakeitimai
2016-03-24 enc28j60

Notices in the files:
parts and their libraries:
SparkFun-DigitalIC: Licensing: CC v3.0 Share-Alike You are welcome to use this library for commercial purposes.
SparkFun-FreqCtrl: Licensing: Creative Commons ShareAlike 4.0 International - https://creativecommons.org/licenses/by-sa/4.0
